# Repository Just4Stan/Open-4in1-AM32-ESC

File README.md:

# Open 4-in-1 AM32 ESC

An open-source 4-in-1 ESC for FPV drones. Runs [AM32](https://github.com/AlkaMotors/AM32-MultiRotor-ESC-firmware) firmware, works with Betaflight over DShot. Designed in KiCad, ready to order from JLCPCB.

I made a video explaining how it works: https://www.youtube.com/watch?v=TwAmmPxOpTM

## Specs

| Parameter | Value |
|---|---|
| Firmware | AM32 |
| Input voltage | 3-6S LiPo (11.1-25.2V) |
| Continuous current | 35A per channel |
| MCU | AT32F421G8U7 (ARM Cortex-M4, 120MHz) |
| Gate driver | NSG2065Q (3-phase, FD6288Q-compatible) |
| MOSFETs | SP40N03GNJ (40V, 2.9mΩ) — optional FDMC8010DC (30V, 1.28mΩ) for premium builds |
| Current sensing | INA186A3IDCKR (100V/V) + 0.2mOhm shunt (165A max) |
| Protocol | DShot (Betaflight compatible) |
| Power supply | LMR51420YDDCR buck + TLV76733DRVR LDO |
| Connector | JST SM08B-SRSS-TB (Betaflight 8-pin standard) |
| PCB | 6-layer, 1oz copper, designed for JLCPCB PCBA |

## Alternative Components

The gate driver footprint is compatible with the entire FD6288Q clone family (27,000+ units combined stock across 7+ manufacturers) and the TI DRV8300. No PCB changes needed for any of them. Multiple pin-compatible MOSFET options are also available, including the FDMC8010DC (30V, 1.28mΩ) as a premium low-resistance option — 36% lower total phase resistance at the cost of reduced voltage headroom (7S max vs 8S+) and higher per-unit cost.

See [ALTERNATIVES.md](ALTERNATIVES.md) for the full list of pin-compatible gate drivers and MOSFETs with LCSC part numbers, specs, and stock levels.

## How it's built

The schematic is split into a main sheet and a sub-sheet that's reused 4 times — one per ESC channel.

The main sheet (`4in1ESC.kicad_sch`) has the power supply, current sensing, and the 8-pin connector. Each ESC channel (`ESC.kicad_sch`) has:
- AT32F421G8U7 running AM32 firmware
- NSG2065Q 3-phase gate driver with bootstrap caps
- 6x SP40N03GNJ MOSFETs in 3 half-bridges
- Back-EMF feedback network for sensorless commutation

## Project structure

```
4in1ESC.kicad_sch     Main schematic (power, sensing, connector)
ESC.kicad_sch         Single ESC channel (used 4x)
4in1ESC.kicad_pcb     PCB layout
4in1ESC.pretty/       Custom footprints
4in1ESC.3dshapes/     3D models (STEP files)
components.kicad_sym  Custom symbols (gate driver, connector, etc.)
datasheets/           Component datasheets
licensing/            Branding and third-party notices
tools/                Analysis scripts
```

## License

Licensed under [CERN-OHL-S-2.0](https://ohwr.org/cern_ohl_s_v2.txt). See [LICENSE](LICENSE) and [licensing/](licensing/) for branding and third-party notices.

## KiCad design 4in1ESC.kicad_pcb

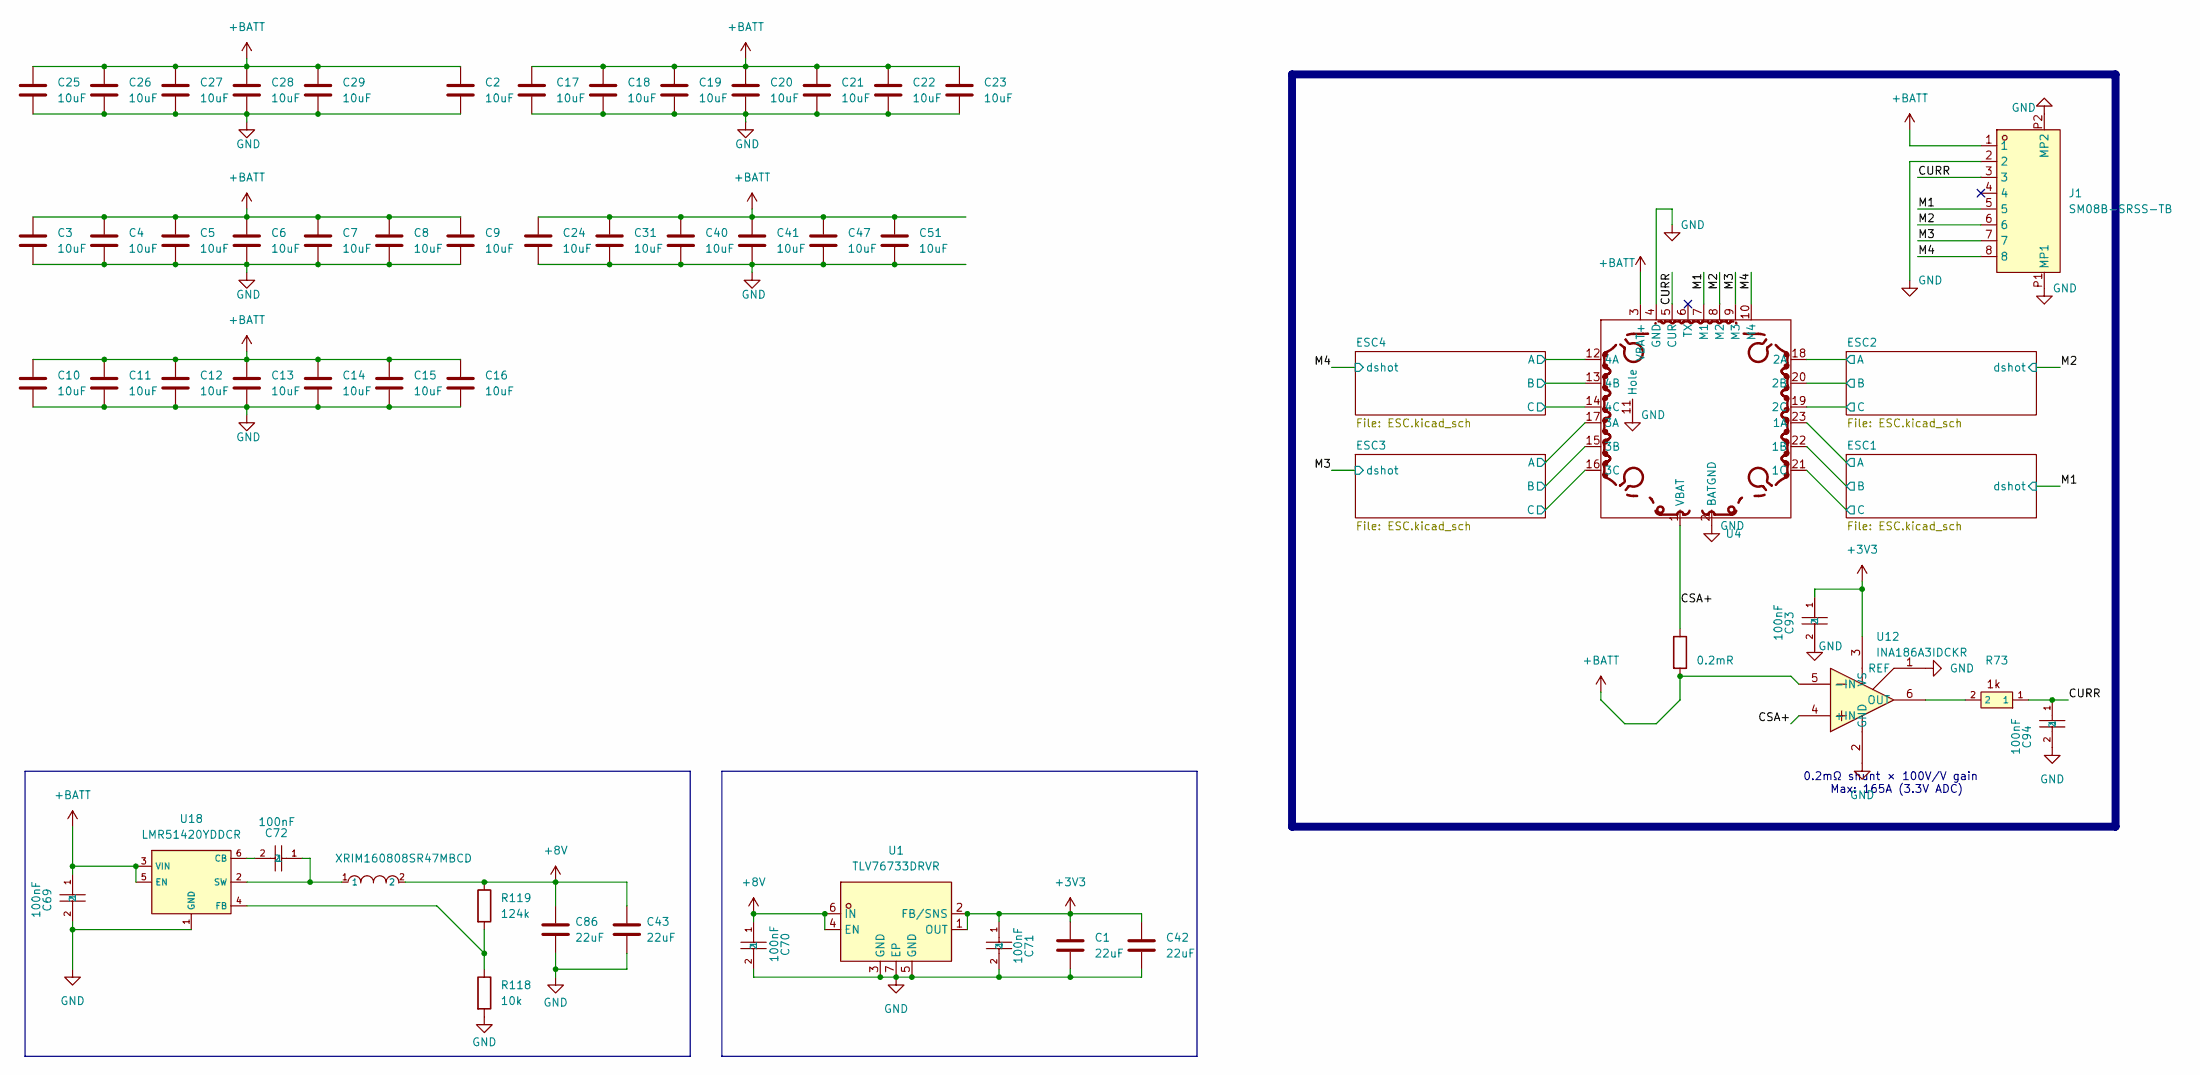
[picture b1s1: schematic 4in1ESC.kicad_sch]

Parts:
C1, C42: 22uF; C_0402_1005Metric; LCSC C105226
C2, C3, C4, C5, C6, C7, C8, C9, C10, C11, C12, C13, C14, C15, C16, C17, C18, C19, C20, C21, C22, C23, C24, C25, C26, C27, C28, C29, C31, C40, C41, C47, C51: 10uF; C_0805_2012Metric; LCSC C2932476
C43, C86: 22uF; C_0603_1608Metric; LCSC C2762594
C69, C70, C71, C72, C93, C94: 100nF; C_0201_0603Metric; LCSC C181043
J1: SM08B-SRSS-TB; JST_SM08B-SRSS-TB; LCSC C160407
R73: 1k; C_0201_0603Metric; LCSC C270365
R118: 10k; C_0201_0603Metric; LCSC C106225
R119: 124k; R_0201_0603Metric; LCSC C423759
Rsense1: 0.2mR; R_2512_6332Metric; LCSC C695806
U1: TLV76733DRVR; WSON-6_L2.0-W2.0-P0.65-TL-EP; LCSC C2848334
U4: 4in1ESC
U5: XRIM160808SR47MBCD; IND-SMD_L1.6-W0.8_FTC160865SR47MBCA; LCSC C48391583
U12: INA186A3IDCKR; SOT-363_SC-70-6; LCSC C2058245
U18: LMR51420YDDCR; SOT-23-6_L2.9-W1.6-P0.95-LS2.9-BL; LCSC C7296200

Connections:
+3V3: C1.2, C42.2, C71.1, C93.1, U1.1 (OUT), U1.2 (FB/SNS), U12.3 (VS); also elsewhere on the board
+8V: C43.1, C70.1, C86.1, R119.1, U1.4 (EN), U1.6 (IN), U5.2; also elsewhere on the board
+BATT: C2.1, C3.1, C4.1, C5.1, C6.1, C7.1, C8.1, C9.1, C10.1, C11.1, C12.1, C13.1, C14.1, C15.1, C16.1, C17.1, C18.1, C19.1, C20.1, C21.1, C22.1, C23.1, C24.1, C25.1, C26.1, C27.1, C28.1, C29.1, C31.1, C40.1, C41.1, C47.1, C51.1, C69.1, J1.1, Rsense1.2, U4.3 (VBAT+), U12.5 (-IN), U18.3 (VIN), U18.5 (EN); also elsewhere on the board
/CSA+: Rsense1.1, U4.1 (VBAT), U12.4 (+IN)
/CURR: C94.1, J1.3, R73.1, U4.5 (CUR)
/ESC1/MotorA: U4.23 (1A); also elsewhere on the board
/ESC1/MotorB: U4.22 (1B); also elsewhere on the board
/ESC1/MotorC: U4.21 (1C); also elsewhere on the board
/ESC2/MotorA: U4.18 (2A); also elsewhere on the board
/ESC2/MotorB: U4.20 (2B); also elsewhere on the board
/ESC2/MotorC: U4.19 (2C); also elsewhere on the board
/ESC3/MotorA: U4.17 (3A); also elsewhere on the board
/ESC3/MotorB: U4.15 (3B); also elsewhere on the board
/ESC3/MotorC: U4.16 (3C); also elsewhere on the board
/ESC4/MotorA: U4.12 (4A); also elsewhere on the board
/ESC4/MotorB: U4.13 (4B); also elsewhere on the board
/ESC4/MotorC: U4.14 (4C); also elsewhere on the board
/M1: J1.5, U4.7 (M1); also elsewhere on the board
/M2: J1.6, U4.8 (M2); also elsewhere on the board
/M3: J1.7, U4.9 (M3); also elsewhere on the board
/M4: J1.8, U4.10 (M4); also elsewhere on the board
GND: C1.1, C2.2, C3.2, C4.2, C5.2, C6.2, C7.2, C8.2, C9.2, C10.2, C11.2, C12.2, C13.2, C14.2, C15.2, C16.2, C17.2, C18.2, C19.2, C20.2, C21.2, C22.2, C23.2, C24.2, C25.2, C26.2, C27.2, C28.2, C29.2, C31.2, C40.2, C41.2, C42.1, C43.2, C47.2, C51.2, C69.2, C70.2, C71.2, C86.2, C93.2, C94.2, J1.2, J1.P1 (MP1), J1.P2 (MP2), R118.2, U1.3 (GND), U1.5 (GND), U1.7 (EP), U4.2 (BATGND), U4.4 (GND), U4.11 (Hole), U12.1 (REF), U12.2 (GND), U18.1 (GND); also elsewhere on the board
unnamed: R73.2, U12.6 (OUT)
unnamed: C72.2, U18.6 (CB)
unnamed: R118.1, R119.2, U18.4 (FB)
unnamed: C72.1, U5.1, U18.2 (SW)

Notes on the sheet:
0.2mΩ shunt × 100V/V gain Max: 165A (3.3V ADC)

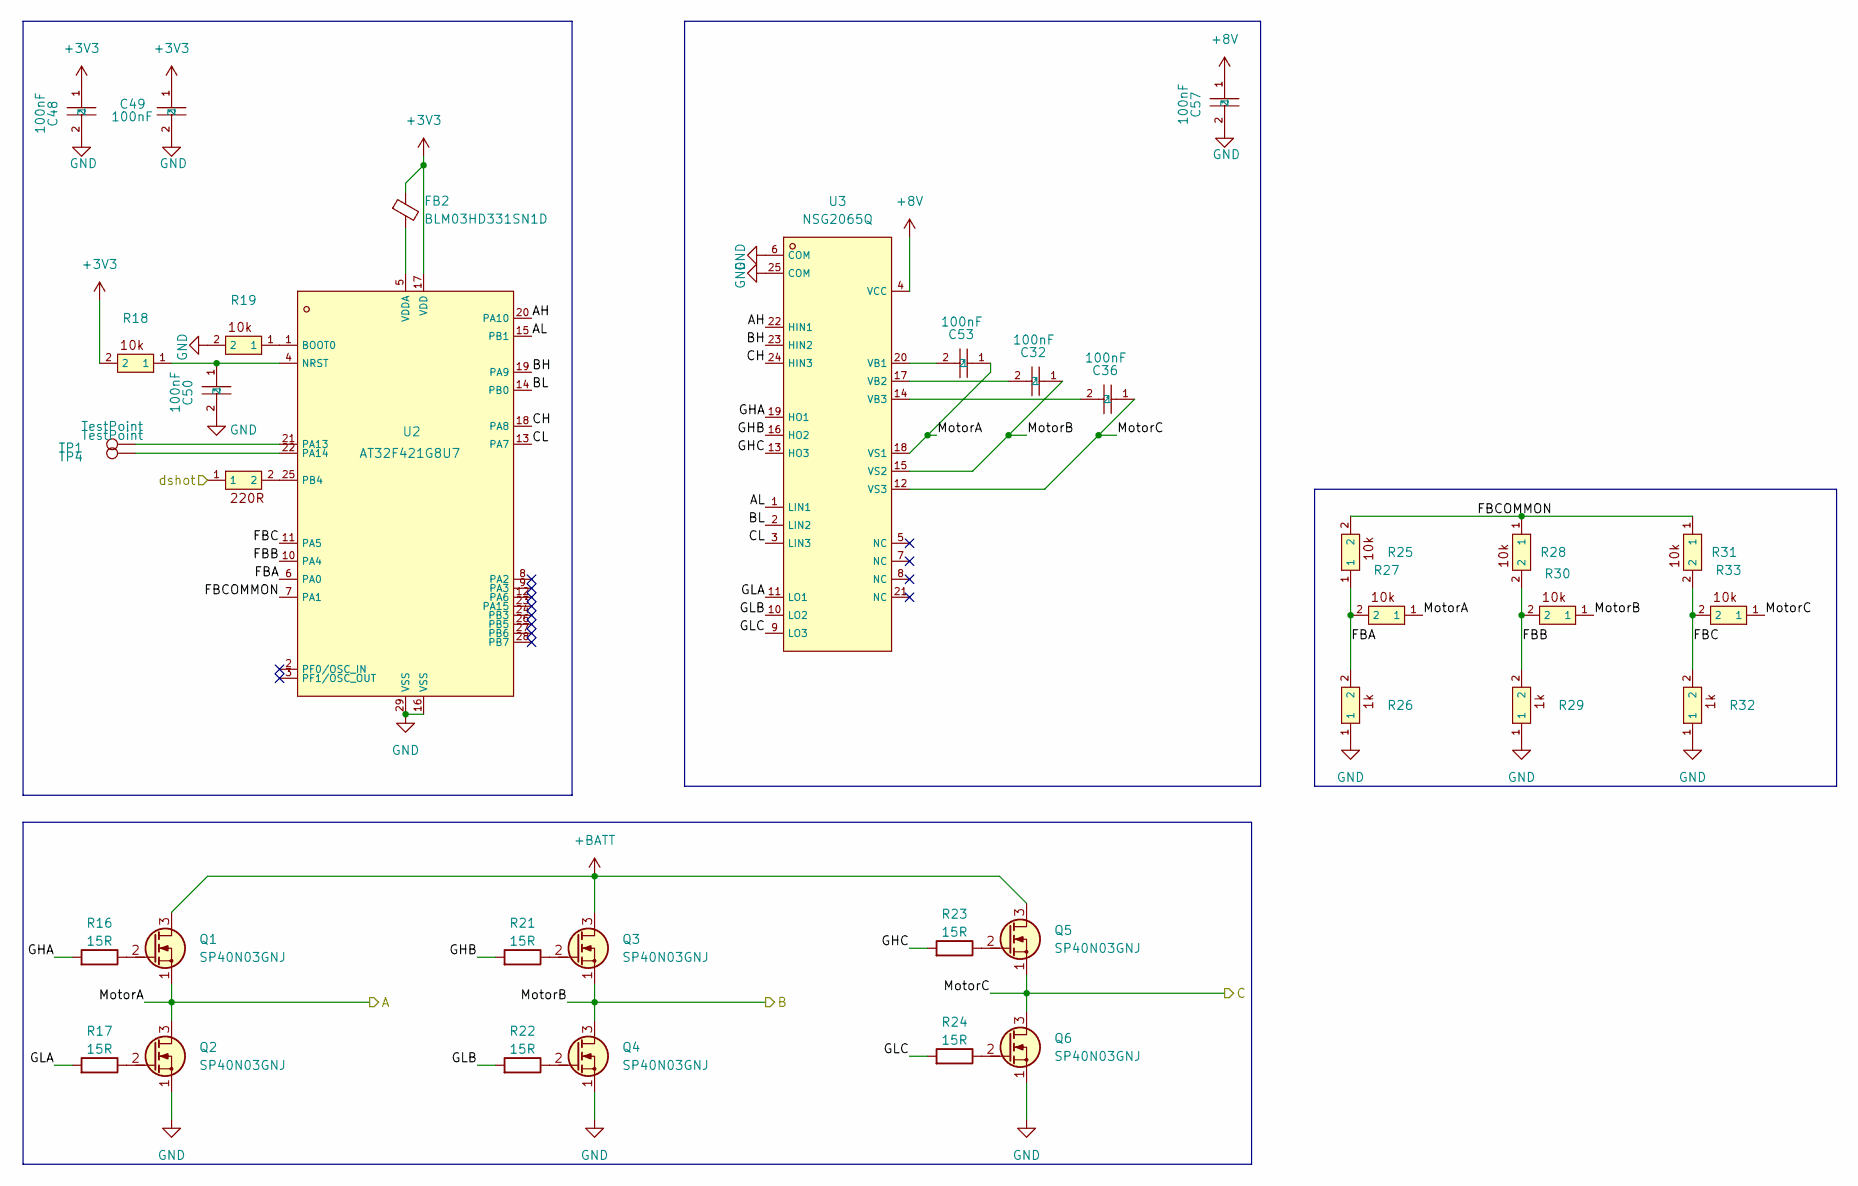
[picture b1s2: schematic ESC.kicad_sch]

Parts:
C32, C36, C53: 100nF; C_0402_1005Metric; LCSC C307331
C48, C49, C50, C57: 100nF; C_0201_0603Metric; LCSC C181043
FB2: BLM03HD331SN1D; L_0201_0603Metric; LCSC C440127
Q1, Q2, Q3, Q4, Q5, Q6: SP40N03GNJ; POWERPAK-1212-8_L3.0-W3.0-P0.65-LS3.3-BL; LCSC C22466709
R16, R17, R21, R22, R23, R24: 15R; C_0201_0603Metric; LCSC C473542
R18, R19, R25, R27, R28, R30, R31, R33: 10k; C_0201_0603Metric; LCSC C106225
R20: 220R; R_0201_0603Metric; LCSC C226468
R26, R29, R32: 1k; C_0201_0603Metric; LCSC C270365
TP1, TP4: TestPoint; TestPoint_Pad_D1.0mm
U2: AT32F421G8U7; QFN-28_L4.0-W4.0-P0.40-TL-EP2.4; LCSC C2765098
U3: NSG2065Q; QFN-24_L4.0-W4.0-P0.50-TL-EP2.8; LCSC C41414478

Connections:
+3V3: C48.1, C49.1, FB2.1, R18.2, U2.17 (VDD); also elsewhere on the board
+8V: C57.1, U3.4 (VCC); also elsewhere on the board
+BATT: Q1.3 (D), Q3.3 (D), Q5.3 (D); also elsewhere on the board
/ESC1/AH: U2.20 (PA10), U3.22 (HIN1)
/ESC1/AL: U2.15 (PB1), U3.1 (LIN1)
/ESC1/BH: U2.19 (PA9), U3.23 (HIN2)
/ESC1/BL: U2.14 (PB0), U3.2 (LIN2)
/ESC1/CH: U2.18 (PA8), U3.24 (HIN3)
/ESC1/CL: U2.13 (PA7), U3.3 (LIN3)
/ESC1/FBA: R25.1, R26.2, R27.2, U2.6 (PA0)
/ESC1/FBB: R28.2, R29.2, R30.2, U2.10 (PA4)
/ESC1/FBC: R31.2, R32.2, R33.2, U2.11 (PA5)
/ESC1/FBCOMMON: R25.2, R28.1, R31.1, U2.7 (PA1)
/ESC1/GHA: R16.1, U3.19 (HO1)
/ESC1/GHB: R21.1, U3.16 (HO2)
/ESC1/GHC: R23.1, U3.13 (HO3)
/ESC1/GLA: R17.1, U3.11 (LO1)
/ESC1/GLB: R22.1, U3.10 (LO2)
/ESC1/GLC: R24.1, U3.9 (LO3)
/ESC1/MotorA: C53.1, Q1.1 (S), Q2.3 (D), R27.1, U3.18 (VS1); also elsewhere on the board
/ESC1/MotorB: C32.1, Q3.1 (S), Q4.3 (D), R30.1, U3.15 (VS2); also elsewhere on the board
/ESC1/MotorC: C36.1, Q5.1 (S), Q6.3 (D), R33.1, U3.12 (VS3); also elsewhere on the board
/M1: R20.1; also elsewhere on the board
GND: C48.2, C49.2, C50.2, C57.2, Q2.1 (S), Q4.1 (S), Q6.1 (S), R19.2, R26.1, R29.1, R32.1, U2.16 (VSS), U2.29 (VSS), U3.6 (COM), U3.25 (COM); also elsewhere on the board
unnamed: Q1.2 (G), R16.2
unnamed: Q2.2 (G), R17.2
unnamed: Q3.2 (G), R21.2
unnamed: Q4.2 (G), R22.2
unnamed: Q5.2 (G), R23.2
unnamed: Q6.2 (G), R24.2
unnamed: R19.1, U2.1 (BOOT0)
unnamed: C50.1, R18.1, U2.4 (NRST)
unnamed: TP1.1, U2.21 (PA13)
unnamed: TP4.1, U2.22 (PA14)
unnamed: R20.2, U2.25 (PB4)
unnamed: FB2.2, U2.5 (VDDA)
unnamed: C53.2, U3.20 (VB1)
unnamed: C32.2, U3.17 (VB2)
unnamed: C36.2, U3.14 (VB3)

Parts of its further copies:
C33, C34, C35, C37, C38, C39, C59, C73, C83: 100nF; C_0402_1005Metric; LCSC C307331
C44, C45, C46, C63, C64, C65, C66, C77, C78, C79, C80, C88: 100nF; C_0201_0603Metric; LCSC C181043
FB1, FB3, FB4: BLM03HD331SN1D; L_0201_0603Metric; LCSC C440127
Q7, Q8, Q9, Q10, Q11, Q12, Q13, Q14, Q15, Q16, Q17, Q18, Q19, Q20, Q21, Q22, Q23, Q24: SP40N03GNJ; POWERPAK-1212-8_L3.0-W3.0-P0.65-LS3.3-BL; LCSC C22466709
R1, R2, R6, R7, R8, R9, R37, R38, R42, R43, R44, R45, R55, R56, R60, R61, R62, R63: 15R; C_0201_0603Metric; LCSC C473542
R3, R4, R10, R12, R13, R15, R34, R36, R39, R40, R46, R48, R49, R51, R52, R54, R57, R58, R64, R66, R67, R69, R70, R72: 10k; C_0201_0603Metric; LCSC C106225
R5, R41, R59: 220R; R_0201_0603Metric; LCSC C226468
R11, R14, R35, R47, R50, R53, R65, R68, R71: 1k; C_0201_0603Metric; LCSC C270365
TP2, TP3, TP5, TP6, TP7, TP8: TestPoint; TestPoint_Pad_D1.0mm
U6, U8, U10: AT32F421G8U7; QFN-28_L4.0-W4.0-P0.40-TL-EP2.4; LCSC C2765098
U7, U9, U11: NSG2065Q; QFN-24_L4.0-W4.0-P0.50-TL-EP2.8; LCSC C41414478

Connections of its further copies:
+3V3: C44.1, C45.1, C64.1, C65.1, C78.1, C79.1, FB1.1, FB3.1, FB4.1, R3.2, R39.2, R57.2, U6.17 (VDD), U8.17 (VDD), U10.17 (VDD); also elsewhere on the board
+8V: C63.1, C77.1, C88.1, U7.4 (VCC), U9.4 (VCC), U11.4 (VCC); also elsewhere on the board
+BATT: Q7.3 (D), Q9.3 (D), Q11.3 (D), Q13.3 (D), Q15.3 (D), Q17.3 (D), Q19.3 (D), Q21.3 (D), Q23.3 (D); also elsewhere on the board
/ESC2/AH: U6.20 (PA10), U7.22 (HIN1)
/ESC2/AL: U6.15 (PB1), U7.1 (LIN1)
/ESC2/BH: U6.19 (PA9), U7.23 (HIN2)
/ESC2/BL: U6.14 (PB0), U7.2 (LIN2)
/ESC2/CH: U6.18 (PA8), U7.24 (HIN3)
/ESC2/CL: U6.13 (PA7), U7.3 (LIN3)
/ESC2/FBA: R10.1, R11.2, R12.2, U6.6 (PA0)
/ESC2/FBB: R13.2, R14.2, R15.2, U6.10 (PA4)
/ESC2/FBC: R34.2, R35.2, R36.2, U6.11 (PA5)
/ESC2/FBCOMMON: R10.2, R13.1, R34.1, U6.7 (PA1)
/ESC2/GHA: R1.1, U7.19 (HO1)
/ESC2/GHB: R6.1, U7.16 (HO2)
/ESC2/GHC: R8.1, U7.13 (HO3)
/ESC2/GLA: R2.1, U7.11 (LO1)
/ESC2/GLB: R7.1, U7.10 (LO2)
/ESC2/GLC: R9.1, U7.9 (LO3)
/ESC2/MotorA: C59.1, Q7.1 (S), Q8.3 (D), R12.1, U7.18 (VS1); also elsewhere on the board
/ESC2/MotorB: C33.1, Q9.1 (S), Q10.3 (D), R15.1, U7.15 (VS2); also elsewhere on the board
/ESC2/MotorC: C37.1, Q11.1 (S), Q12.3 (D), R36.1, U7.12 (VS3); also elsewhere on the board
/ESC3/AH: U8.20 (PA10), U9.22 (HIN1)
/ESC3/AL: U8.15 (PB1), U9.1 (LIN1)
/ESC3/BH: U8.19 (PA9), U9.23 (HIN2)
/ESC3/BL: U8.14 (PB0), U9.2 (LIN2)
/ESC3/CH: U8.18 (PA8), U9.24 (HIN3)
/ESC3/CL: U8.13 (PA7), U9.3 (LIN3)
/ESC3/FBA: R46.1, R47.2, R48.2, U8.6 (PA0)
/ESC3/FBB: R49.2, R50.2, R51.2, U8.10 (PA4)
/ESC3/FBC: R52.2, R53.2, R54.2, U8.11 (PA5)
/ESC3/FBCOMMON: R46.2, R49.1, R52.1, U8.7 (PA1)
/ESC3/GHA: R37.1, U9.19 (HO1)
/ESC3/GHB: R42.1, U9.16 (HO2)
/ESC3/GHC: R44.1, U9.13 (HO3)
/ESC3/GLA: R38.1, U9.11 (LO1)
/ESC3/GLB: R43.1, U9.10 (LO2)
/ESC3/GLC: R45.1, U9.9 (LO3)
/ESC3/MotorA: C73.1, Q13.1 (S), Q14.3 (D), R48.1, U9.18 (VS1); also elsewhere on the board
/ESC3/MotorB: C34.1, Q15.1 (S), Q16.3 (D), R51.1, U9.15 (VS2); also elsewhere on the board
/ESC3/MotorC: C38.1, Q17.1 (S), Q18.3 (D), R54.1, U9.12 (VS3); also elsewhere on the board
/ESC4/AH: U10.20 (PA10), U11.22 (HIN1)
/ESC4/AL: U10.15 (PB1), U11.1 (LIN1)
/ESC4/BH: U10.19 (PA9), U11.23 (HIN2)
/ESC4/BL: U10.14 (PB0), U11.2 (LIN2)
/ESC4/CH: U10.18 (PA8), U11.24 (HIN3)
/ESC4/CL: U10.13 (PA7), U11.3 (LIN3)
/ESC4/FBA: R64.1, R65.2, R66.2, U10.6 (PA0)
/ESC4/FBB: R67.2, R68.2, R69.2, U10.10 (PA4)
/ESC4/FBC: R70.2, R71.2, R72.2, U10.11 (PA5)
/ESC4/FBCOMMON: R64.2, R67.1, R70.1, U10.7 (PA1)
/ESC4/GHA: R55.1, U11.19 (HO1)
/ESC4/GHB: R60.1, U11.16 (HO2)
/ESC4/GHC: R62.1, U11.13 (HO3)
/ESC4/GLA: R56.1, U11.11 (LO1)
/ESC4/GLB: R61.1, U11.10 (LO2)
/ESC4/GLC: R63.1, U11.9 (LO3)
/ESC4/MotorA: C83.1, Q19.1 (S), Q20.3 (D), R66.1, U11.18 (VS1); also elsewhere on the board
/ESC4/MotorB: C35.1, Q21.1 (S), Q22.3 (D), R69.1, U11.15 (VS2); also elsewhere on the board
/ESC4/MotorC: C39.1, Q23.1 (S), Q24.3 (D), R72.1, U11.12 (VS3); also elsewhere on the board
/M2: R5.1; also elsewhere on the board
/M3: R41.1; also elsewhere on the board
/M4: R59.1; also elsewhere on the board
GND: C44.2, C45.2, C46.2, C63.2, C64.2, C65.2, C66.2, C77.2, C78.2, C79.2, C80.2, C88.2, Q8.1 (S), Q10.1 (S), Q12.1 (S), Q14.1 (S), Q16.1 (S), Q18.1 (S), Q20.1 (S), Q22.1 (S), Q24.1 (S), R4.2, R11.1, R14.1, R35.1, R40.2, R47.1, R50.1, R53.1, R58.2, R65.1, R68.1, R71.1, U6.16 (VSS), U6.29 (VSS), U7.6 (COM), U7.25 (COM), U8.16 (VSS), U8.29 (VSS), U9.6 (COM), U9.25 (COM), U10.16 (VSS), U10.29 (VSS), U11.6 (COM), U11.25 (COM); also elsewhere on the board
unnamed: Q7.2 (G), R1.2
unnamed: Q8.2 (G), R2.2
unnamed: Q9.2 (G), R6.2
unnamed: Q10.2 (G), R7.2
unnamed: Q11.2 (G), R8.2
unnamed: Q12.2 (G), R9.2
unnamed: Q13.2 (G), R37.2
unnamed: Q14.2 (G), R38.2
unnamed: Q15.2 (G), R42.2
unnamed: Q16.2 (G), R43.2
unnamed: Q17.2 (G), R44.2
unnamed: Q18.2 (G), R45.2
unnamed: Q19.2 (G), R55.2
unnamed: Q20.2 (G), R56.2
unnamed: Q21.2 (G), R60.2
unnamed: Q22.2 (G), R61.2
unnamed: Q23.2 (G), R62.2
unnamed: Q24.2 (G), R63.2
unnamed: R4.1, U6.1 (BOOT0)
unnamed: C46.1, R3.1, U6.4 (NRST)
unnamed: TP2.1, U6.21 (PA13)
unnamed: TP3.1, U6.22 (PA14)
unnamed: R5.2, U6.25 (PB4)
unnamed: FB1.2, U6.5 (VDDA)
unnamed: C59.2, U7.20 (VB1)
unnamed: C33.2, U7.17 (VB2)
unnamed: C37.2, U7.14 (VB3)
unnamed: R40.1, U8.1 (BOOT0)
unnamed: C66.1, R39.1, U8.4 (NRST)
unnamed: TP5.1, U8.21 (PA13)
unnamed: TP6.1, U8.22 (PA14)
unnamed: R41.2, U8.25 (PB4)
unnamed: FB3.2, U8.5 (VDDA)
unnamed: C73.2, U9.20 (VB1)
unnamed: C34.2, U9.17 (VB2)
unnamed: C38.2, U9.14 (VB3)
unnamed: R58.1, U10.1 (BOOT0)
unnamed: C80.1, R57.1, U10.4 (NRST)
unnamed: TP7.1, U10.21 (PA13)
unnamed: TP8.1, U10.22 (PA14)
unnamed: R59.2, U10.25 (PB4)
unnamed: FB4.2, U10.5 (VDDA)
unnamed: C83.2, U11.20 (VB1)
unnamed: C35.2, U11.17 (VB2)
unnamed: C39.2, U11.14 (VB3)

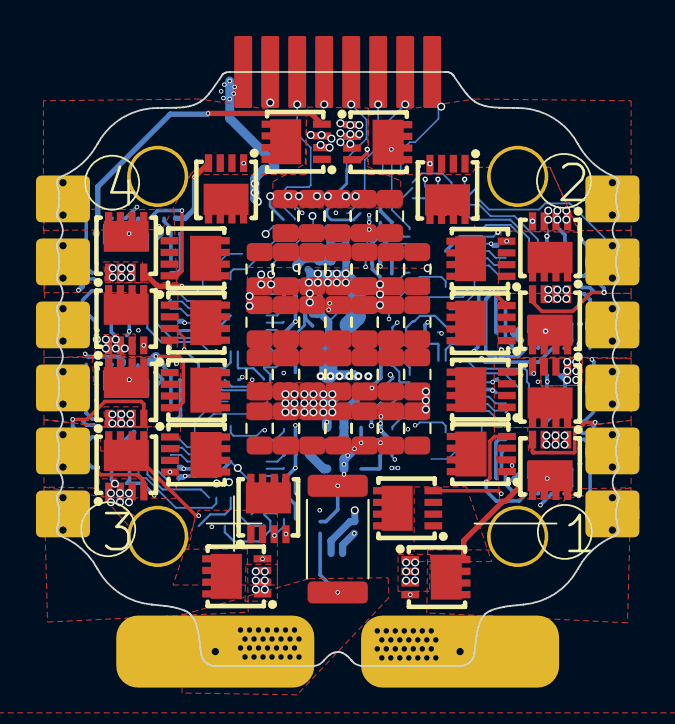
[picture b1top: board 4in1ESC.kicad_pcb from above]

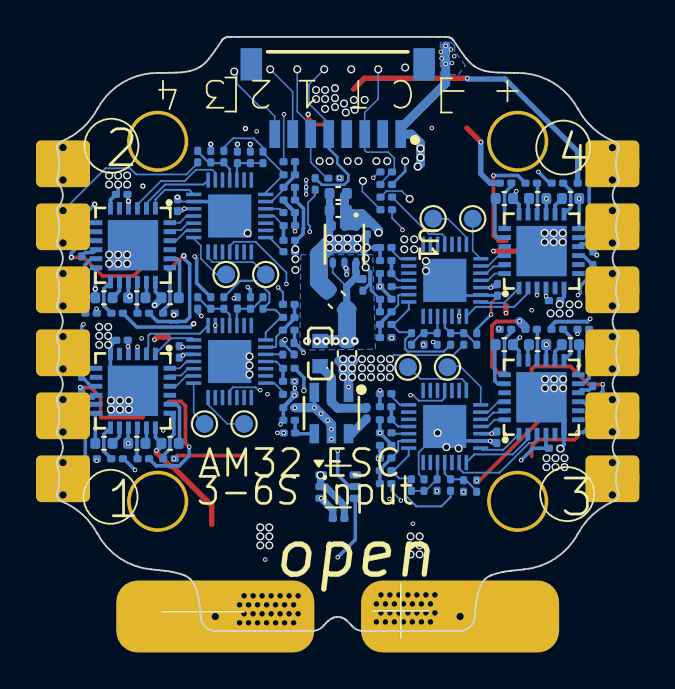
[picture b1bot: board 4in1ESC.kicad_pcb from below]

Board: 6 copper layers, 31.2 x 33.0 mm, 197 parts (138 on the bottom side), 150 nets.

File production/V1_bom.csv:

Designator,Footprint,Quantity,Value,LCSC Part #
"C1, C42",0402,2,22uF,C105226
"C10, C11, C12, C13, C14, C15, C16, C17, C18, C19, C2, C20, C21, C22, C23, C24, C25, C26, C27, C28, C29, C3, C31, C4, C40, C41, C47, C5, C51, C6, C7, C8, C9",0805,33,10uF,C440198
"C32, C33, C34, C35, C36, C37, C38, C39, C53, C59, C73, C83",0402,12,100nF,C307331
"C43, C86",0603,2,22uF,C2762594
"C44, C45, C46, C48, C49, C50, C57, C63, C64, C65, C66, C69, C70, C71, C72, C77, C78, C79, C80, C88, C93, C94",0201,22,100nF,C181043
"FB1, FB2, FB3, FB4",0201,4,BLM03PX121SN1D,C525479
J1,JST_SM08B-SRSS-TB,1,SM08B-SRSS-TB,C160407
"Q1, Q10, Q11, Q12, Q13, Q14, Q15, Q16, Q17, Q18, Q19, Q2, Q20, Q21, Q22, Q23, Q24, Q3, Q4, Q5, Q6, Q7, Q8, Q9",POWERPAK-1212-8_L3.0-W3.0-P0.65-LS3.3-BL,24,SP40N03GNJ,C22466709
"R1, R16, R17, R2, R21, R22, R23, R24, R37, R38, R42, R43, R44, R45, R55, R56, R6, R60, R61, R62, R63, R7, R8, R9",0201,24,15R,C473542
"R10, R118, R12, R13, R15, R18, R19, R25, R27, R28, R3, R30, R31, R33, R34, R36, R39, R4, R40, R46, R48, R49, R51, R52, R54, R57, R58, R64, R66, R67, R69, R70, R72",0201,33,10k,C473048
"R11, R14, R26, R29, R32, R35, R47, R50, R53, R65, R68, R71, R73",0201,13,1k,C270365
R119,0201,1,124k,C423759
"R20, R41, R5, R59",0201,4,220R,C473535
RSENSE1,2512,1,0.2mR,C695806
"TP1, TP2, TP3, TP4, TP5, TP6, TP7, TP8",TestPoint_Pad_D1.0mm,8,TestPoint,
U1,WSON-6_L2.0-W2.0-P0.65-TL-EP,1,TLV76733DRVR,C2848334
"U10, U2, U6, U8",QFN-28_L4.0-W4.0-P0.40-TL-EP2.4,4,AT32F421G8U7,C2765098
"U11, U3, U7, U9",QFN-24_L4.0-W4.0-P0.50-TL-EP2.8,4,NSG2065Q,C41414478
U12,SOT-363_SC-70-6,1,INA186A3IDCKR,C2058245
U18,SOT-23-6_L2.9-W1.6-P0.95-LS2.9-BL,1,LMR51420YDDCR,C7296200
U4,4in1ESC,1,~,
U5,IND-SMD_L1.6-W0.8_FTC160865SR47MBCA,1,XRIM160808SR47MBCD,C48391583

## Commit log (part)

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2026-03-09 made it
2026-03-09 Update PCB layer count in README
    Updated PCB layer count from 4-layer to 6-layer.
2026-03-11 Replaced the old ESC Connector with JST-SH series
2026-03-11 update readme n datasheets
2026-03-14 Added many compatibilty and fixed all issues, ready for ordering V1
2026-03-14 final layout
2026-03-16 Parts changes and final production files for V1
